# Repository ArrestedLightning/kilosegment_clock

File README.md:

Kilosegment Clock
==================

Contents of the Firmware directory is licensed under GPLv3.

All other content in this repository is licensed under CC BY 4.0.

Acknowledgments
=================

Firmware for this project is based substantially on John Bradnam's work here: https://create.arduino.cc/projecthub/john-bradnam/7-segment-array-clock-cd5b07

His project, in turn, was based in part upon Frugha's project here: https://hackaday.io/project/169632-7-segment-display-array-clock

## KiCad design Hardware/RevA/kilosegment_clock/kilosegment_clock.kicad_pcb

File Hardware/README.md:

Kilosegment Clock Hardware
===============

Rev A and Rev B should be functionally identical.  Rev A is designed with individual 7-segment displays, and Rev B uses 4-digit displays, which substantially reduces the number of through-hole pins that need to be soldered.

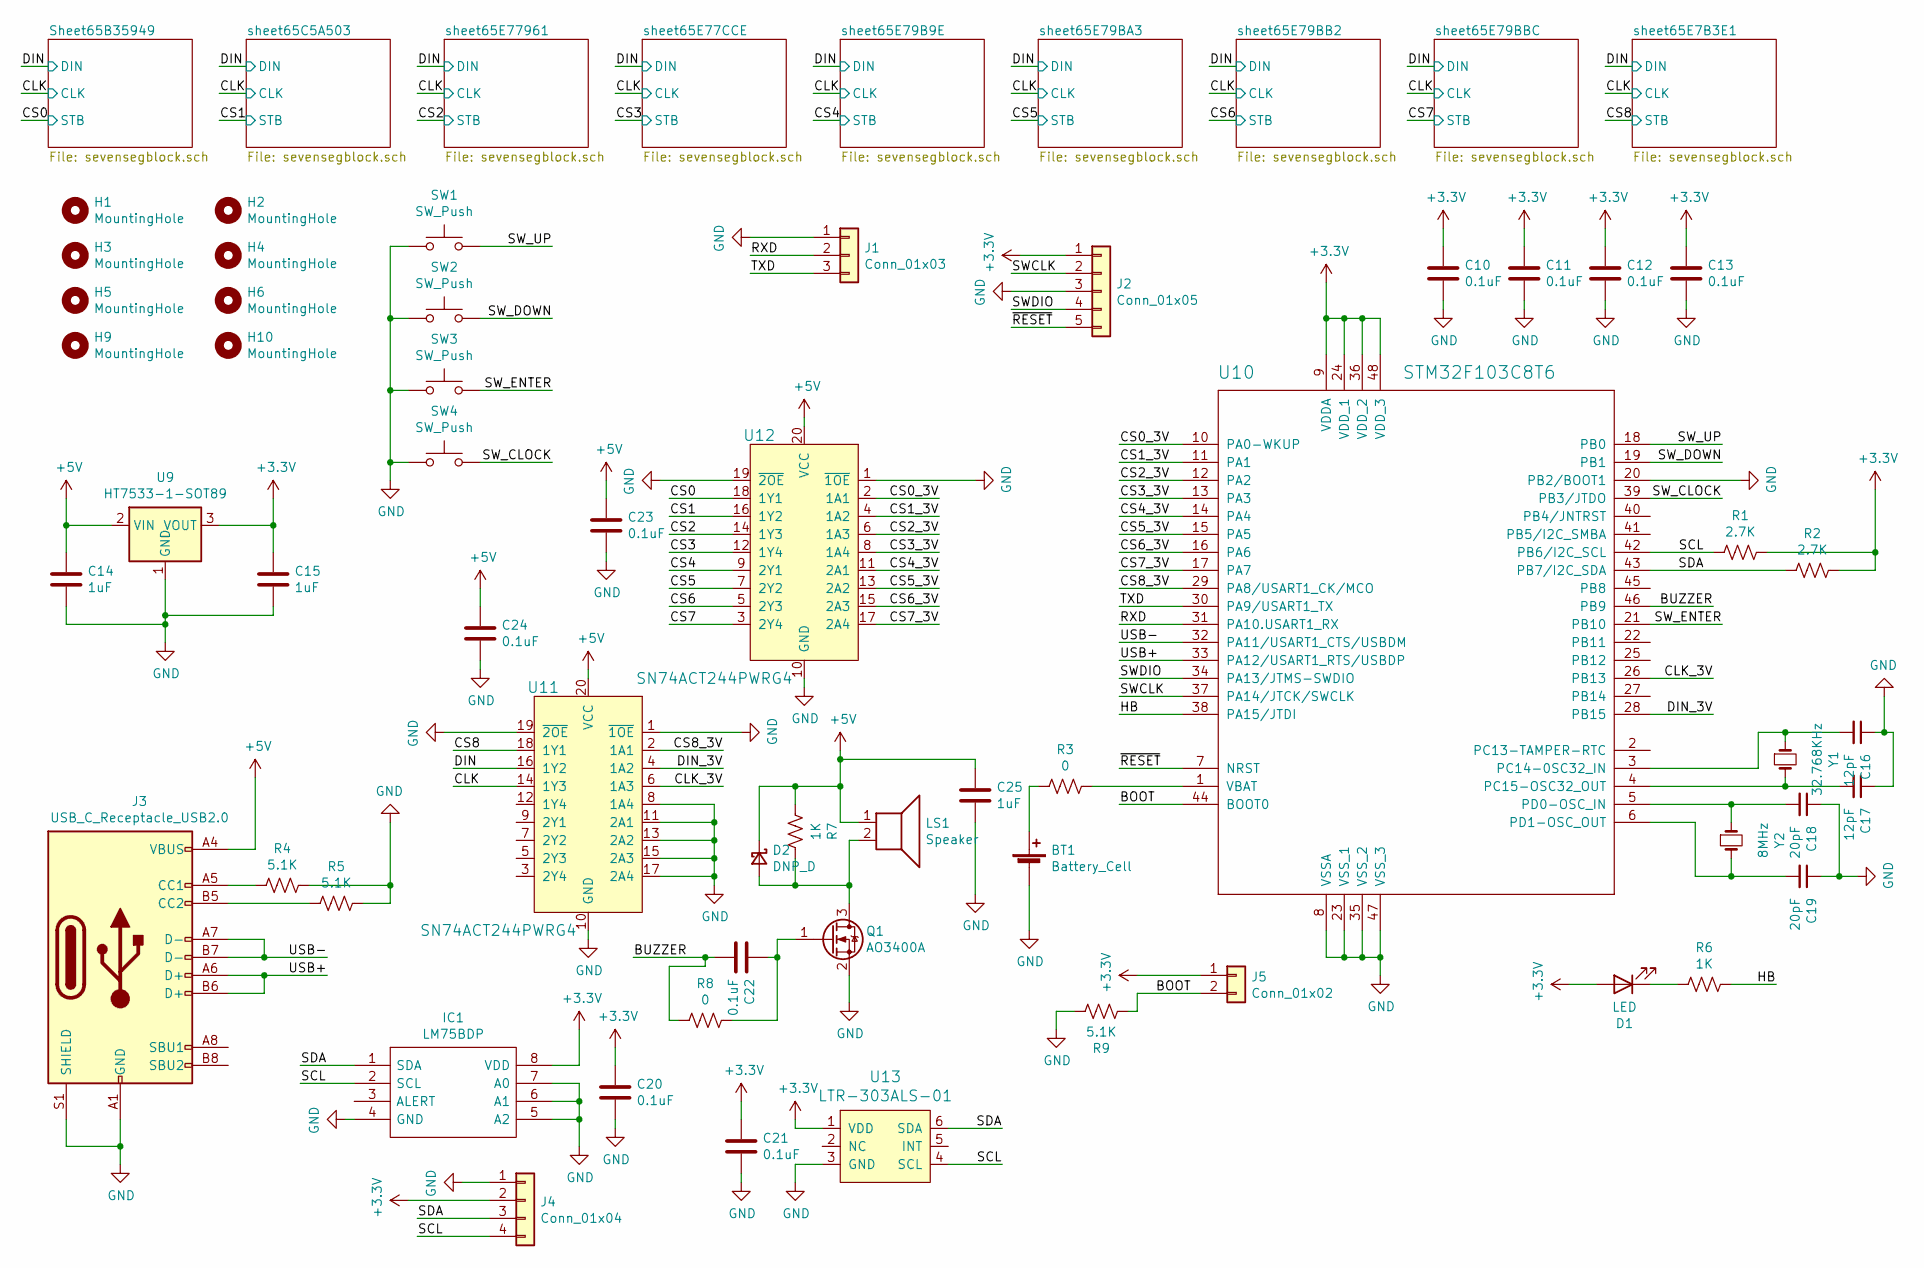
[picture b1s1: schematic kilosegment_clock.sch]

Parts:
BT1: Battery_Cell; BatteryHolder_CR2032-BS-6-1_1x2032; Digikey BH-49A-5-T-BK
C10, C11, C12, C13, C20, C21, C22, C23, C24: 0.1uF; C_0805_2012Metric_Pad1.18x1.45mm_HandSolder; Digikey 1276-1003-1-ND
C14, C15, C25: 1uF; C_0805_2012Metric_Pad1.18x1.45mm_HandSolder; Digikey 1276-1026-1-ND
C16, C17: 12pF; C_0805_2012Metric_Pad1.18x1.45mm_HandSolder; Digikey CML0805C0G120JT50V
C18, C19: 20pF; C_0805_2012Metric_Pad1.18x1.45mm_HandSolder; Digikey 738-CML0805C0G200JT50VCT-ND
D1: LED; LED_0805_2012Metric_Pad1.15x1.40mm_HandSolder; Digikey 754-1132-1-ND
D2: DNP_D; D_SOD-123
H1, H2, H3, H4, H5, H6, H9, H10: MountingHole; pcb_nut_m3
IC1: LM75BDP; MSOP-8_3x3mm_P0.65mm; Digikey 568-4768-1-ND
J1: Conn_01x03; PinHeader_1x03_P2.54mm_Vertical
J2: Conn_01x05; PinHeader_1x05_P2.54mm_Vertical
J3: USB_C_Receptacle_USB2.0; USB_C_Receptacle_HRO_TYPE-C-31-M-12; Digikey 664-12402012E212ACT-ND
J4: Conn_01x04; PinHeader_1x04_P2.54mm_Vertical
J5: Conn_01x02; PinHeader_1x02_P2.54mm_Vertical
LS1: Speaker; BUZ-TH_PKM13EPYH4002-B0; Digikey 490-4697-ND
Q1: AO3400A; SOT-23_Handsoldering; LCSC Part C20917
R1, R2: 2.7K; R_0805_2012Metric_Pad1.20x1.40mm_HandSolder; Digikey RMCF0805FT2K70CT-ND
R3, R8: 0; R_0805_2012Metric_Pad1.20x1.40mm_HandSolder; Digikey RMCF0805ZT0R00CT-ND
R4, R5, R9: 5.1K; R_0805_2012Metric_Pad1.20x1.40mm_HandSolder; Digikey RMCF0805FT5K10CT-ND
R6, R7: 1K; R_0805_2012Metric_Pad1.20x1.40mm_HandSolder; Digikey RMCF0805FT1K00CT-ND
SW1, SW2, SW3, SW4: SW_Push; SW_SPST_TL3342; Digikey CKN12222-1-ND
U9: HT7533-1-SOT89; SOT-89-3; Digikey 2129-RH5RL33AA-T1-FECT-ND
U10: STM32F103C8T6; LQFP-48_7x7mm_P0.5mm; Digikey 497-11517-ND
U11, U12: SN74ACT244PWRG4; TSSOP-20_4.4x6.5mm_P0.65mm; LCSC Part C6930
U13: LTR-303ALS-01; SOT-363_SC-70-6_Handsoldering; LCSC Part C364577
Y1: 32.768KHz; Crystal_SMD_3215-2Pin_3.2x1.5mm; Digikey 9H03200031-ND
Y2: 8MHz; Crystal_SMD_5032-2Pin_5.0x3.2mm_HandSoldering; Digikey XC2103CT-ND

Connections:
+3V3: C10.1, C11.1, C12.1, C13.1, C15.1, C20.1, C21.1, D1.2 (A), IC1.8 (VDD), J2.1, J4.2, J5.1, R1.1, R2.1, U9.3 (VOUT), U10.9 (VDDA), U10.24 (VDD_1), U10.36 (VDD_2), U10.48 (VDD_3), U13.1 (VDD)
+5V: C14.1, C23.1, C24.1, C25.1, D2.1 (K), J3.A4 (VBUS), J3.A9 (VBUS), J3.B4 (VBUS), J3.B9 (VBUS), LS1.1, R7.2, U9.2 (VIN), U11.20 (VCC), U12.20 (VCC); also elsewhere on the board
/BOOT: J5.2, R9.2, U10.44 (BOOT0)
/BUZZER: C22.2, R8.2, U10.46 (PB9)
/CLK: U11.14 (1Y3); also elsewhere on the board
/CLK_3V: U10.26 (PB13), U11.6 (1A3)
/CS0: U12.18 (1Y1); also elsewhere on the board
/CS0_3V: U10.10 (PA0-WKUP), U12.2 (1A1)
/CS1: U12.16 (1Y2); also elsewhere on the board
/CS1_3V: U10.11 (PA1), U12.4 (1A2)
/CS2: U12.14 (1Y3); also elsewhere on the board
/CS2_3V: U10.12 (PA2), U12.6 (1A3)
/CS3: U12.12 (1Y4); also elsewhere on the board
/CS3_3V: U10.13 (PA3), U12.8 (1A4)
/CS4: U12.9 (2Y1); also elsewhere on the board
/CS4_3V: U10.14 (PA4), U12.11 (2A1)
/CS5: U12.7 (2Y2); also elsewhere on the board
/CS5_3V: U10.15 (PA5), U12.13 (2A2)
/CS6: U12.5 (2Y3); also elsewhere on the board
/CS6_3V: U10.16 (PA6), U12.15 (2A3)
/CS7: U12.3 (2Y4); also elsewhere on the board
/CS7_3V: U10.17 (PA7), U12.17 (2A4)
/CS8: U11.18 (1Y1); also elsewhere on the board
/CS8_3V: U10.29 (PA8/USART1_CK/MCO), U11.2 (1A1)
/DIN: U11.16 (1Y2); also elsewhere on the board
/DIN_3V: U10.28 (PB15), U11.4 (1A2)
/HB: R6.1, U10.38 (PA15/JTDI)
/RXD: J1.2, U10.31 (PA10.USART1_RX)
/SCL: IC1.2 (SCL), J4.4, R1.2, U10.42 (PB6/I2C_SCL), U13.4 (SCL)
/SDA: IC1.1 (SDA), J4.3, R2.2, U10.43 (PB7/I2C_SDA), U13.6 (SDA)
/SWCLK: J2.2, U10.37 (PA14/JTCK/SWCLK)
/SWDIO: J2.4, U10.34 (PA13/JTMS-SWDIO)
/SW_CLOCK: SW4.2, U10.39 (PB3/JTDO)
/SW_DOWN: SW2.2, U10.19 (PB1)
/SW_ENTER: SW3.2, U10.21 (PB10)
/SW_UP: SW1.2, U10.18 (PB0)
/TXD: J1.3, U10.30 (PA9/USART1_TX)
/USB+: J3.A6 (D+), J3.B6 (D+), U10.33 (PA12/USART1_RTS/USBDP)
/USB-: J3.A7 (D-), J3.B7 (D-), U10.32 (PA11/USART1_CTS/USBDM)
/~RESET: J2.5, U10.7 (NRST)
GND: BT1.2 (-), C10.2, C11.2, C12.2, C13.2, C14.2, C15.2, C16.1, C17.1, C18.1, C19.1, C20.2, C21.2, C23.2, C24.2, C25.2, IC1.4 (GND), IC1.5 (A2), IC1.6 (A1), IC1.7 (A0), J1.1, J2.3, J3.A1 (GND), J3.A12 (GND), J3.B1 (GND), J3.B12 (GND), J3.S1 (SHIELD), J4.1, Q1.2 (S), R4.1, R5.1, R9.1, SW1.1, SW2.1, SW3.1, SW4.1, U9.1 (GND), U10.8 (VSSA), U10.20 (PB2/BOOT1), U10.23 (VSS_1), U10.35 (VSS_2), U10.47 (VSS_3), U11.1 (~1OE), U11.8 (1A4), U11.10 (GND), U11.11 (2A1), U11.13 (2A2), U11.15 (2A3), U11.17 (2A4), U11.19 (~2OE), U12.1 (~1OE), U12.10 (GND), U12.19 (~2OE), U13.3 (GND); also elsewhere on the board
unnamed: BT1.1 (+), R3.2
unnamed: C16.2, U10.3 (PC14-0SC32_IN), Y1.1
unnamed: C17.2, U10.4 (PC15-OSC32_OUT), Y1.2
unnamed: C18.2, U10.5 (PD0-OSC_IN), Y2.1
unnamed: C19.2, U10.6 (PD1-OSC_OUT), Y2.2
unnamed: C22.1, Q1.1 (G), R8.1
unnamed: D1.1 (K), R6.2
unnamed: D2.2 (A), LS1.2, Q1.3 (D), R7.1
unnamed: J3.A5 (CC1), R4.2
unnamed: J3.B5 (CC2), R5.2
unnamed: R3.1, U10.1 (VBAT)
